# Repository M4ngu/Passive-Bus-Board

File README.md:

# Passive-Bus-Board

This is a passive eurorack bus board, with on board 5v regulation and double power terminal for daisy chaining multiple boards.

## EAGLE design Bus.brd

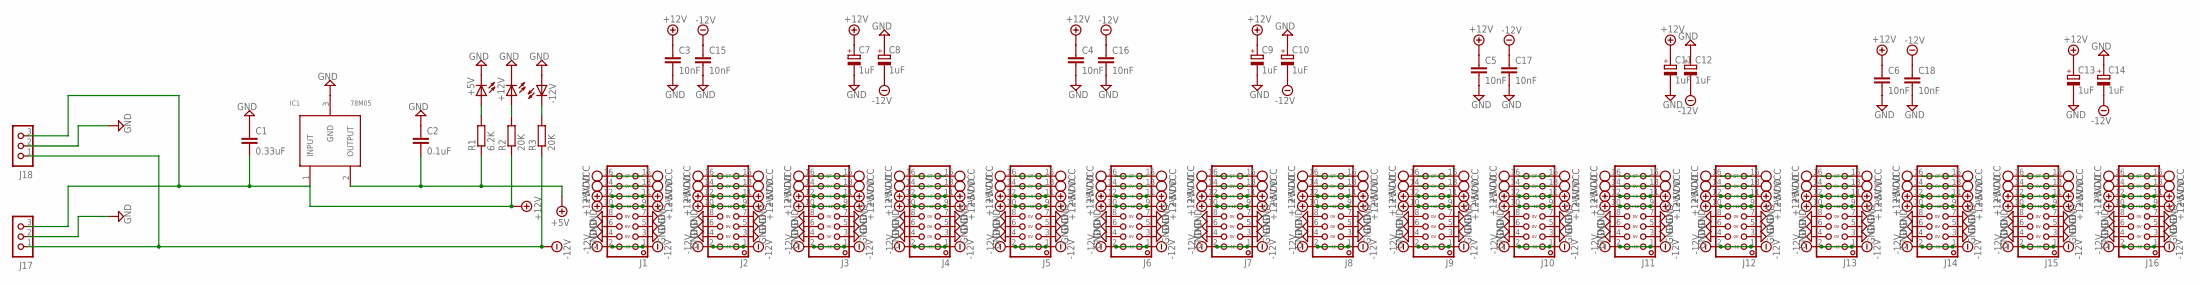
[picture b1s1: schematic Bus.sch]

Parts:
+5V, +12V: LED3MM
-12V: LED3MM
C1: 0.33uF; C1206
C2: 0.1uF; C1206
C3, C4, C5, C6, C15, C16, C17, C18: 10nF; C1206
C7, C8, C9, C10, C11, C12, C13, C14: 1uF; PANASONIC_A
IC1: 78M05; TO252
J1, J2, J3, J4, J5, J6, J7, J8, J9, J10, J11, J12, J13, J14, J15, J16: EUROPWR_2X08-SHROUD; 2X08_EUROPWR_SHROUD
J17, J18: CON_TERMINAL_BLOCK_03-5MM; TERMINAL_BLOCK_3P_5
R1: 6.2K; R1206
R2, R3: 20K; R1206

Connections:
+5V: C2.2, IC1.2 (OUTPUT), J1.11, J1.12, J2.11, J2.12, J3.11, J3.12, J4.11, J4.12, J5.11, J5.12, J6.11, J6.12, J7.11, J7.12, J8.11, J8.12, J9.11, J9.12, J10.11, J10.12, J11.11, J11.12, J12.11, J12.12, J13.11, J13.12, J14.11, J14.12, J15.11, J15.12, J16.11, J16.12, R1.1
+12V: C1.2, C3.1, C4.1, C5.1, C6.1, C7.+, C9.+, C11.+, C13.+, IC1.1 (INPUT), J1.9, J1.10, J2.9, J2.10, J3.9, J3.10, J4.9, J4.10, J5.9, J5.10, J6.9, J6.10, J7.9, J7.10, J8.9, J8.10, J9.9, J9.10, J10.9, J10.10, J11.9, J11.10, J12.9, J12.10, J13.9, J13.10, J14.9, J14.10, J15.9, J15.10, J16.9, J16.10, J17.3, J18.3, R2.1
-12V: C8.-, C10.-, C12.-, C14.-, C15.1, C16.1, C17.1, C18.1, J1.1, J1.2, J2.1, J2.2, J3.1, J3.2, J4.1, J4.2, J5.1, J5.2, J6.1, J6.2, J7.1, J7.2, J8.1, J8.2, J9.1, J9.2, J10.1, J10.2, J11.1, J11.2, J12.1, J12.2, J13.1, J13.2, J14.1, J14.2, J15.1, J15.2, J16.1, J16.2, J17.1, J18.1, R3.1
MT: +5V.K (C), +12V.K (C), -12V.A, C1.1, C2.1, C3.2, C4.2, C5.2, C6.2, C7.-, C8.+, C9.-, C10.+, C11.-, C12.+, C13.-, C14.+, C15.2, C16.2, C17.2, C18.2, IC1.3 (GND), J1.3, J1.4, J1.5, J1.6, J1.7, J1.8, J2.3, J2.4, J2.5, J2.6, J2.7, J2.8, J3.3, J3.4, J3.5, J3.6, J3.7, J3.8, J4.3, J4.4, J4.5, J4.6, J4.7, J4.8, J5.3, J5.4, J5.5, J5.6, J5.7, J5.8, J6.3, J6.4, J6.5, J6.6, J6.7, J6.8, J7.3, J7.4, J7.5, J7.6, J7.7, J7.8, J8.3, J8.4, J8.5, J8.6, J8.7, J8.8, J9.3, J9.4, J9.5, J9.6, J9.7, J9.8, J10.3, J10.4, J10.5, J10.6, J10.7, J10.8, J11.3, J11.4, J11.5, J11.6, J11.7, J11.8, J12.3, J12.4, J12.5, J12.6, J12.7, J12.8, J13.3, J13.4, J13.5, J13.6, J13.7, J13.8, J14.3, J14.4, J14.5, J14.6, J14.7, J14.8, J15.3, J15.4, J15.5, J15.6, J15.7, J15.8, J16.3, J16.4, J16.5, J16.6, J16.7, J16.8, J17.2, J18.2
unnamed: +5V.A, R1.2
unnamed: +12V.A, R2.2
unnamed: -12V.K (C), R3.2
VCC: J1.15, J1.16, J2.15, J2.16, J3.15, J3.16, J4.15, J4.16, J5.15, J5.16, J6.15, J6.16, J7.15, J7.16, J8.15, J8.16, J9.15, J9.16, J10.15, J10.16, J11.15, J11.16, J12.15, J12.16, J13.15, J13.16, J14.15, J14.16, J15.15, J15.16, J16.15, J16.16
VDD: J1.13, J1.14, J2.13, J2.14, J3.13, J3.14, J4.13, J4.14, J5.13, J5.14, J6.13, J6.14, J7.13, J7.14, J8.13, J8.14, J9.13, J9.14, J10.13, J10.14, J11.13, J11.14, J12.13, J12.14, J13.13, J13.14, J14.13, J14.14, J15.13, J15.14, J16.13, J16.14

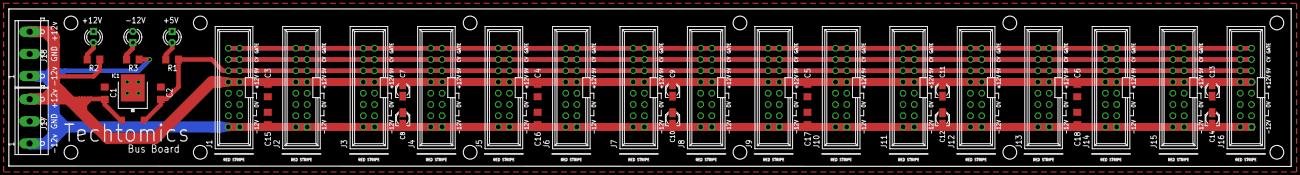
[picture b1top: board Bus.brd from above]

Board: 2 copper layers, 289.7 x 35.6 mm, 43 parts (0 on the bottom side), 9 nets.
